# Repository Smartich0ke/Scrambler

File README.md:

# Arduino-powered cube scrambler

I go to a school where speed-cubing is popular and a no-phones policy is enforced during lunch break. This device consists of a cutom-designed PCB with a 128x64 OLED display and an ATMega328P chip and generates a random scramble algorithm speedcubing solves can be fair, consistent and retain a level of officiality without the need for a phone app to generate the scrambles.

## The PCB
The PCB is made up of 3 core components:

 * **The user interface** - A 128x64 SSD1306 display to display the scrambles and 3 pushbuttons to navigate the screen's interface
 * **The microcontroller** - An ATmega328P chip to control everything
 * **The LiPo charge circuit** - A Microchip MCP73831 chip to charge a small lithium battery that powers the rest of the board. It is charged via a micro USB port.

The PCB was designed in KiCad. You can find the KiCad files in `pcb/kicad`. You can also find pre-made Gerber files in `pcb/gerbers` for production.

## The code

The code is written using the Arduino framework and the Adafruit SSD1306 library. A `platformio.ini` file is provided for use in PlatformIO and is the reccomended way ot compile and upload the code to this device.

## How to make a scrambler

### A. Make/assemble the board

#### Bill Of Materials (BOM):
 * X1 ATmega328P
 * X1 128x64 OLED display
 * X1 MCP73831
 * X2 10uF electrolytic capacitors
 * X2 4.7uF electrolytic cpacitors
 * X3 6mm pushbutton switches
 * X1 Digikey Micro USB type B connector

 1. Download the necesarry files: `git clone https://github.com/Smartich0ke/Scrambler.git`
 2. Open up the KiCad project in `pcb/kicad/scrambler.kicad_pro`. Open the PCB layout editor and export the necesarry gerbers and adjust the settings in the export window depending on your PCB manufacturer.
 3. Send the files to your PCB manufacturer and get it made.
 4.  4. Solder in the components into their corresponding places according to the BOM above.

### B. Compile and upload the code
 1. Open the root directory of the git repo in PlatformIO VScode extention
 2. In the PlatformIO Tasks menu, double-click "build" under upload_USBTINY
### C. 3D-print the case
*coming soon*

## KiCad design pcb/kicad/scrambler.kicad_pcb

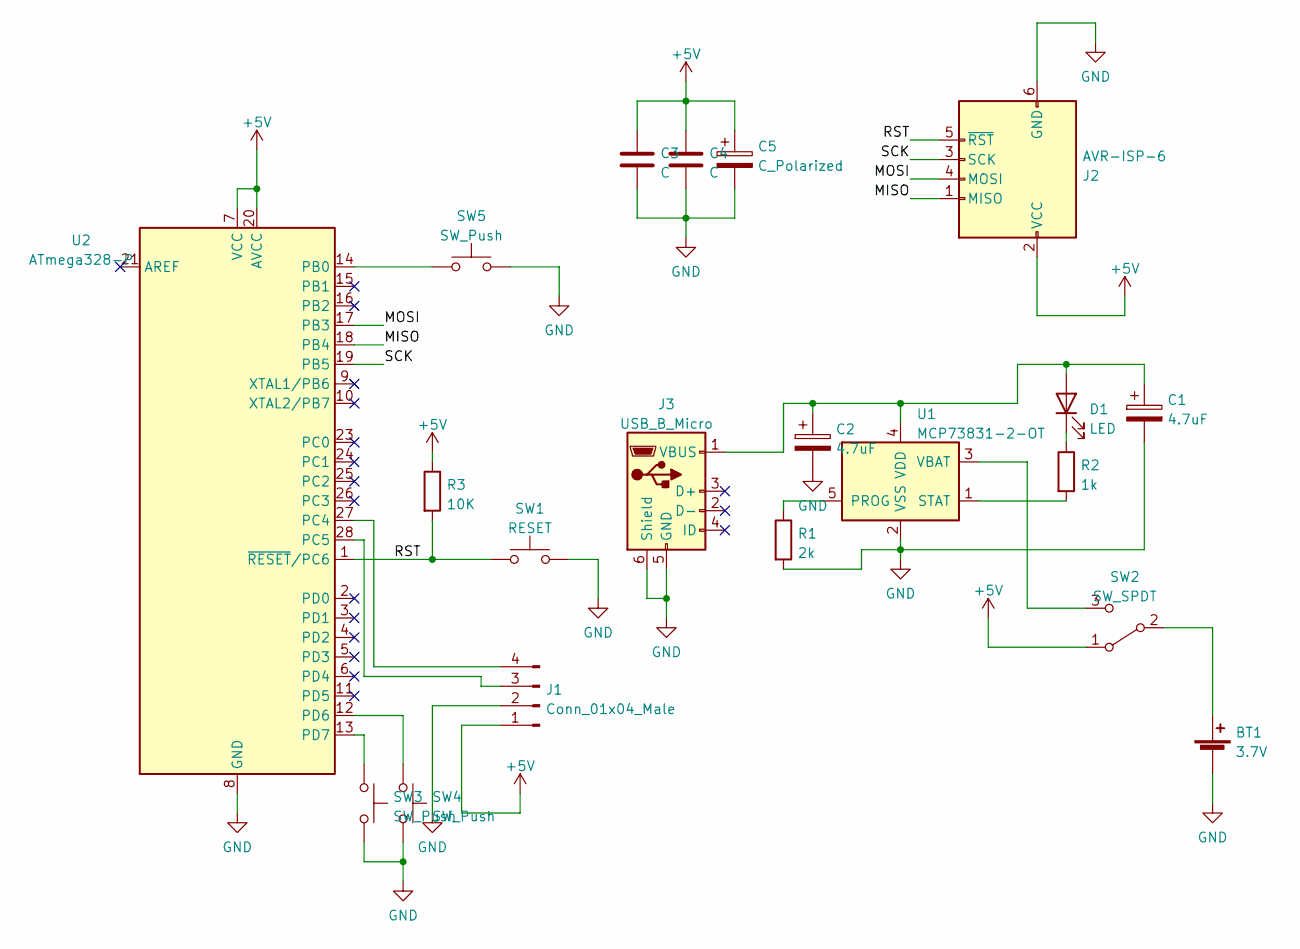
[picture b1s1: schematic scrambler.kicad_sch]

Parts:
BT1: 3.7V; PinHeader_1x02_P2.54mm_Vertical
C1, C2: 4.7uF; CP_Radial_D5.0mm_P2.50mm
C3, C4: C; C_Disc_D6.0mm_W2.5mm_P5.00mm
C5: C_Polarized; CP_Radial_D5.0mm_P2.50mm
D1: LED; LED_D3.0mm
J1: Conn_01x04_Male; PinHeader_1x04_P2.54mm_Vertical
J2: AVR-ISP-6; PinHeader_2x03_P2.54mm_Vertical
J3: USB_B_Micro; USB_Micro-B_Molex_47346-0001
R1: 2k; R_Axial_DIN0207_L6.3mm_D2.5mm_P7.62mm_Horizontal
R2: 1k; R_Axial_DIN0207_L6.3mm_D2.5mm_P7.62mm_Horizontal
R3: 10K; R_Axial_DIN0207_L6.3mm_D2.5mm_P7.62mm_Horizontal
SW1: RESET; SW_PUSH_6mm
SW2: SW_SPDT; SLIDE-SWITCH
SW3, SW4, SW5: SW_Push; SW_PUSH_6mm
U1: MCP73831-2-OT; SOT-23-5
U2: ATmega328-P; DIP-28_W7.62mm

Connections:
+5V: C3.1, C4.1, C5.1, J1.1, J2.2 (VCC), R3.1, SW2.1 (A), U2.7 (VCC), U2.20 (AVCC)
/MISO: J2.1 (MISO), U2.18 (PB4)
/MOSI: J2.4 (MOSI), U2.17 (PB3)
/RST: J2.5 (~RST), R3.2, SW1.1, U2.1 (~RESET/PC6)
/SCK: J2.3 (SCK), U2.19 (PB5)
GND: BT1.2 (-), C1.2, C2.2, C3.2, C4.2, C5.2, J1.2, J2.6 (GND), J3.5 (GND), J3.6 (Shield), R1.2, SW1.2, SW3.2, SW4.2, SW5.2, U1.2 (VSS), U2.8 (GND), U2.22 (GND)
unnamed: BT1.1 (+), SW2.2 (B)
unnamed: C1.1, C2.1, D1.2 (A), J3.1 (VBUS), U1.4 (VDD)
unnamed: D1.1 (K), R2.1
unnamed: J1.3, U2.28 (PC5)
unnamed: J1.4, U2.27 (PC4)
unnamed: R1.1, U1.5 (PROG)
unnamed: R2.2, U1.1 (STAT)
unnamed: SW2.3 (C), U1.3 (VBAT)
unnamed: SW4.1, U2.12 (PD6)
unnamed: SW3.1, U2.13 (PD7)
unnamed: SW5.1, U2.14 (PB0)

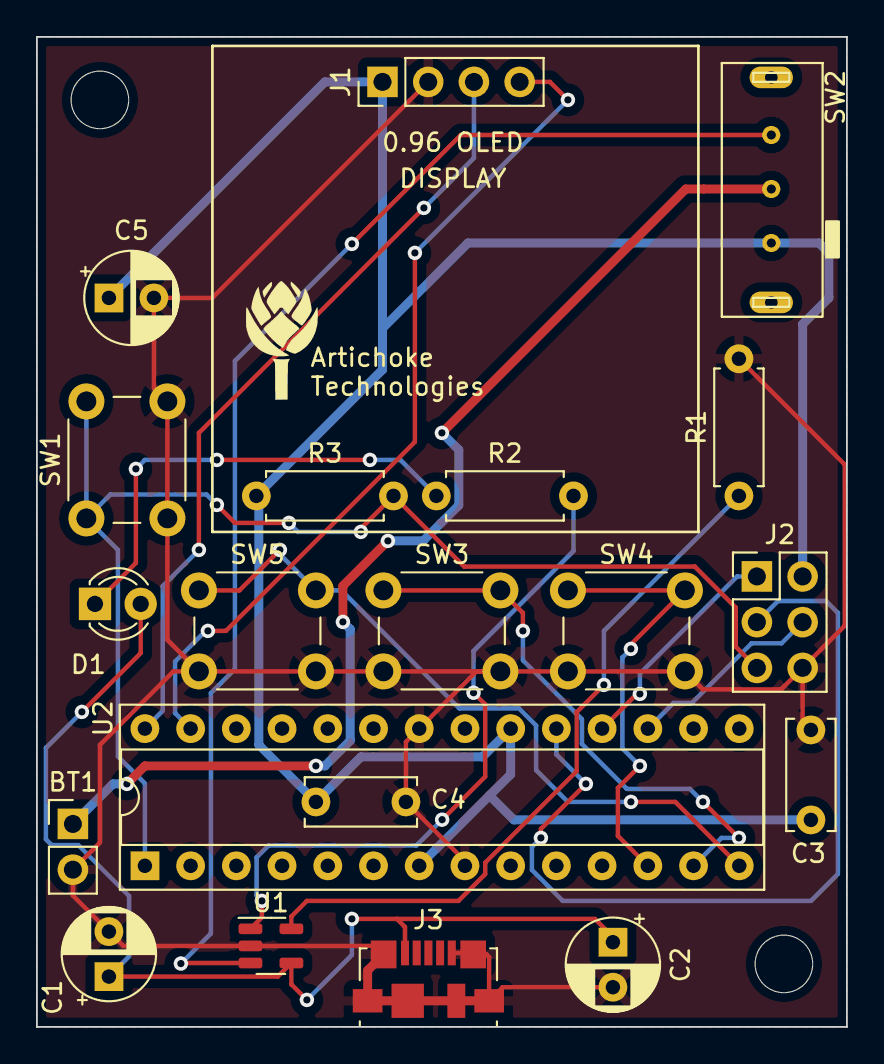
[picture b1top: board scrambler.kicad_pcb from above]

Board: 2 copper layers, 45.0 x 55.0 mm, 20 parts (0 on the bottom side), 17 nets.

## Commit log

2022-05-29 reset variables on scramble
2022-05-29 ingore those pesky DS_Store files
2022-05-29 add kicad board files and gerbers
2022-05-31 add main content ro readme
2022-05-31 add more steps to readme
